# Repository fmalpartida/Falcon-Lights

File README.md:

# Falcon-Lights
Bandai 1:144 Millenium Falcon Light kit driver. 

This is a small board that retorfits into LED light compartment of the Bandai 1:144 Millenium Falcon kit.

The main difference between the original kit is its capability of driving upto to 6 white LEDs running from 2 AAAA batteries and fitting the whole assembly into the original compartment inside the Falcon.

## 3D Renders
Top

Bottom

## Geek Kids Project
The board has been developed by electronFUN under the Geek Kids initiative. 

The Geek Kids initiative is a local electroFUN project where we try to bring youngsters close to technology. Kids under the initiative get exposed to technology projects while participating in them and bring up to speed for sharing with the general public. 

All the benefits derived from Geek Kids projects will revert back to the initiative and will help them develop more stuff and reachout to more kids.

All these projects are released under the Geek Kids logo and are Open Source for everyone to enjoy. 

Stay tunned.

## Where to get them
We don't have intentions to sell them and encourrage you to build them by yourself. If you would like us to build one for you please let me know by sending me a message, we will be delighted to build one for you.

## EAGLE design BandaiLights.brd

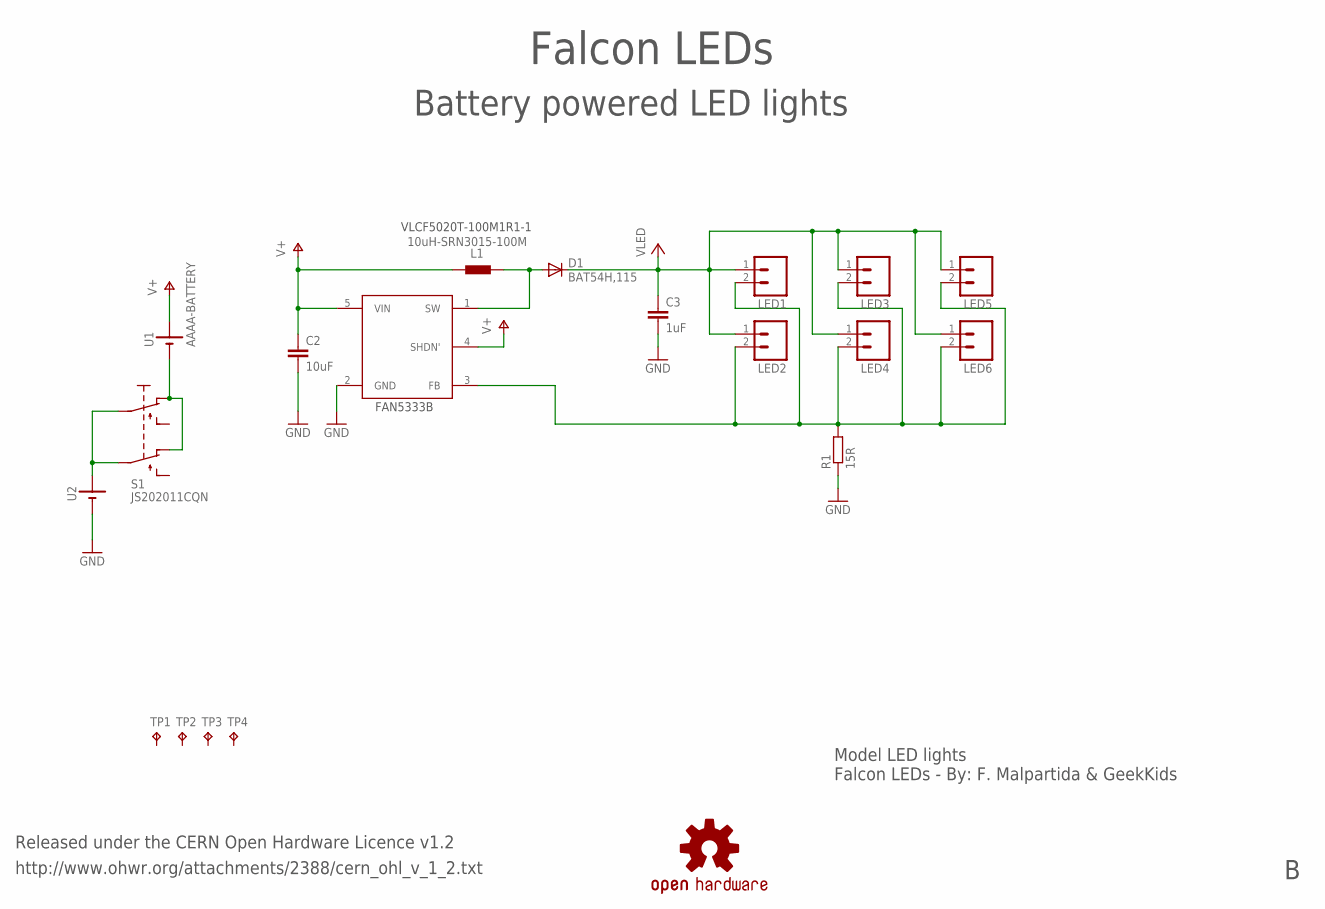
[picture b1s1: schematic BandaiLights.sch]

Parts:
C2: 10uF; C1206
C3: 1uF; C0805
D1: BAT54H,115; SOD123
L1: 10uH-SRN3015-100M; LQH
LED1, LED2, LED3, LED4, LED5, LED6: M02PTH; 1X02
Q1: FAN5333B; SOT23-5
R1: 15R; M0805
S1: JS202011CQN; SWITCH-JS202011
TP1, TP2, TP3, TP4: TPB1,27; B1,27
U1, U2: AAAA-BATTERY; 51-AAAA
U$4: SPARKFUN_OSHW-LOGOM; SPARKFUN_OSHW-LOGO-M

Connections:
FB: LED1.2, LED2.2, LED3.2, LED4.2, LED5.2, LED6.2, Q1.3 (FB), R1.2
GND: C2.2, C3.2, Q1.2 (GND), R1.1, U2.P3 (-), U2.P4 (-)
unnamed: D1.A, L1.2, Q1.1 (SW)
unnamed: S1.P2, S1.P5 (P1), U2.P1 (+), U2.P2 (+)
unnamed: S1.P1 (O), S1.P4 (O1), U1.P3 (-), U1.P4 (-)
V+: C2.1, L1.1, Q1.4 (SHDN'), Q1.5 (VIN), U1.P1 (+), U1.P2 (+)
VCC: C3.1, D1.C, LED1.1, LED2.1, LED3.1, LED4.1, LED5.1, LED6.1

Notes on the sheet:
FAN5333B
Model LED lights Falcon LEDs - By: F. Malpartida & GeekKids
Battery powered LED lights
Released under the CERN Open Hardware Licence v1.2
http://www.ohwr.org/attachments/2388/cern_ohl_v_1_2.txt
VLCF5020T-100M1R1-1
Falcon LEDs

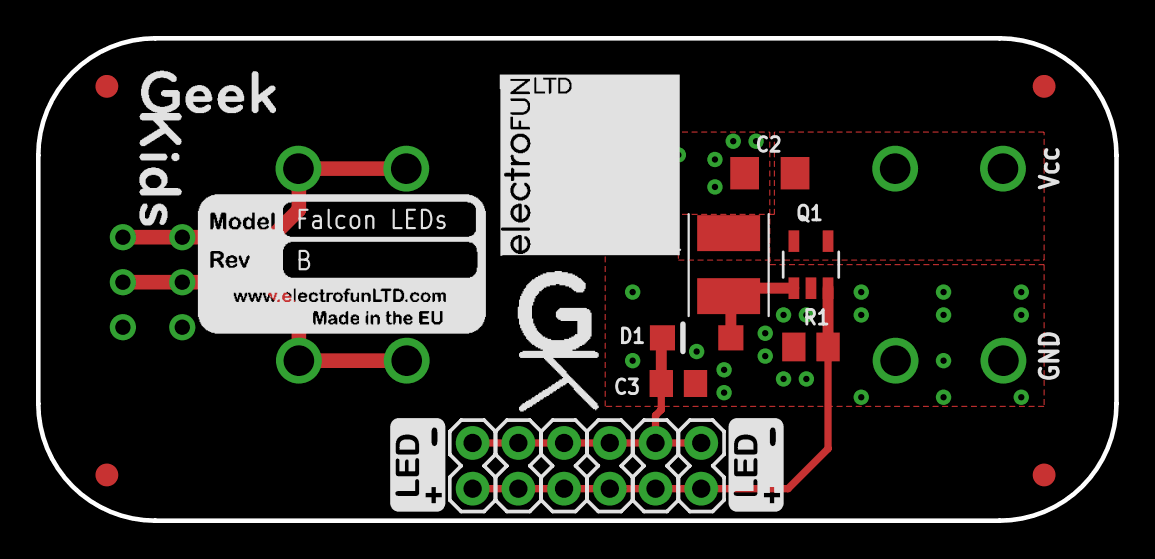
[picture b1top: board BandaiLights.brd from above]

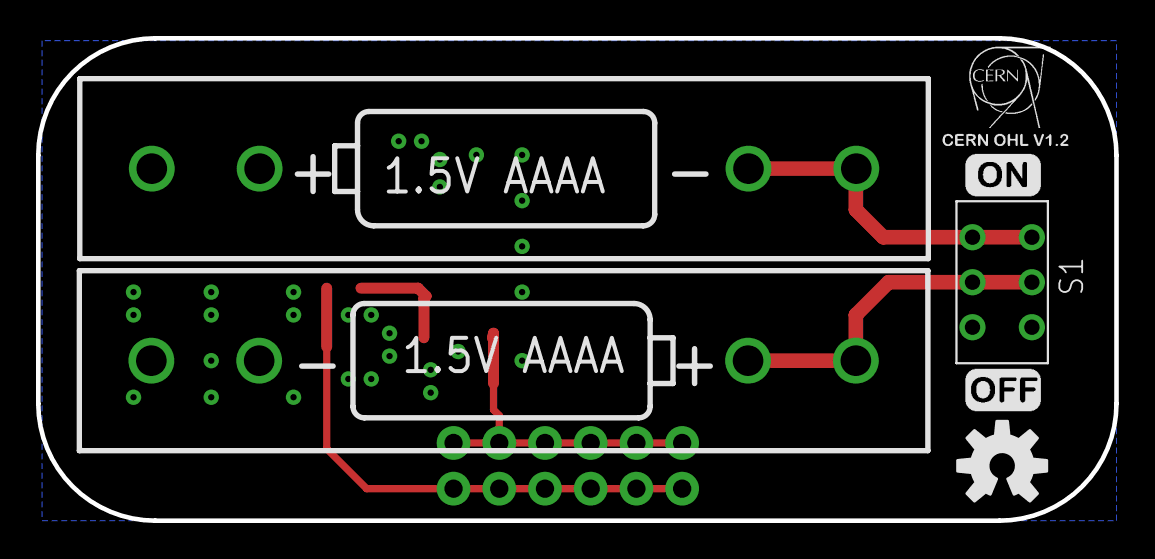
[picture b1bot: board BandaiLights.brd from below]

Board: 2 copper layers, 59.9 x 26.8 mm, 29 parts (7 on the bottom side), 7 nets.

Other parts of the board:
U$1: CERN_OHL
U$2: ON
U$3: ELECTROFUN_10X10
U$5: BOARD_INFO_BMP_SMALL
U$6: OFF
U$8, U$11: LED_SILK
U$9: GEEKKIDS_S
U$10: GEEKKIDS_LOGO_S

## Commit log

2016-02-21 PCB Revision A
2016-02-21 Revised PCB: - Revised LED layout to avoid having to rework the interior of the Falcon to fit all 6 LEDs - Revised silk screen to make it more readable. - Added GK (geek kids logo).
    Added license.
2016-02-21 Updated license description.
2016-02-21 Create gh-pages branch via GitHub
2016-02-21 Added short description.
2016-02-21 Fixed image URL.
2016-02-21 Updated read.
2016-02-21 Fixed image links.
2016-02-21 Added GK logo and images.
2016-02-21 Fixed GK logo size.
2016-02-21 Updated PCB revision image in the project.
2016-02-21 Added comments to read.
2016-02-21 Added Geek Kids logo.
2016-02-22 Release Rev B, untested.
2016-02-22 Removed gerbers till tested.
2016-06-19 Update contents.
2016-06-19 Updated schematics.
2016-06-19 Updated LED setup to be in parallel.

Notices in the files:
parts and their libraries:
SparkFun: Licensing: CC v3.0 Share-Alike You are welcome to use this library for commercial purposes.
